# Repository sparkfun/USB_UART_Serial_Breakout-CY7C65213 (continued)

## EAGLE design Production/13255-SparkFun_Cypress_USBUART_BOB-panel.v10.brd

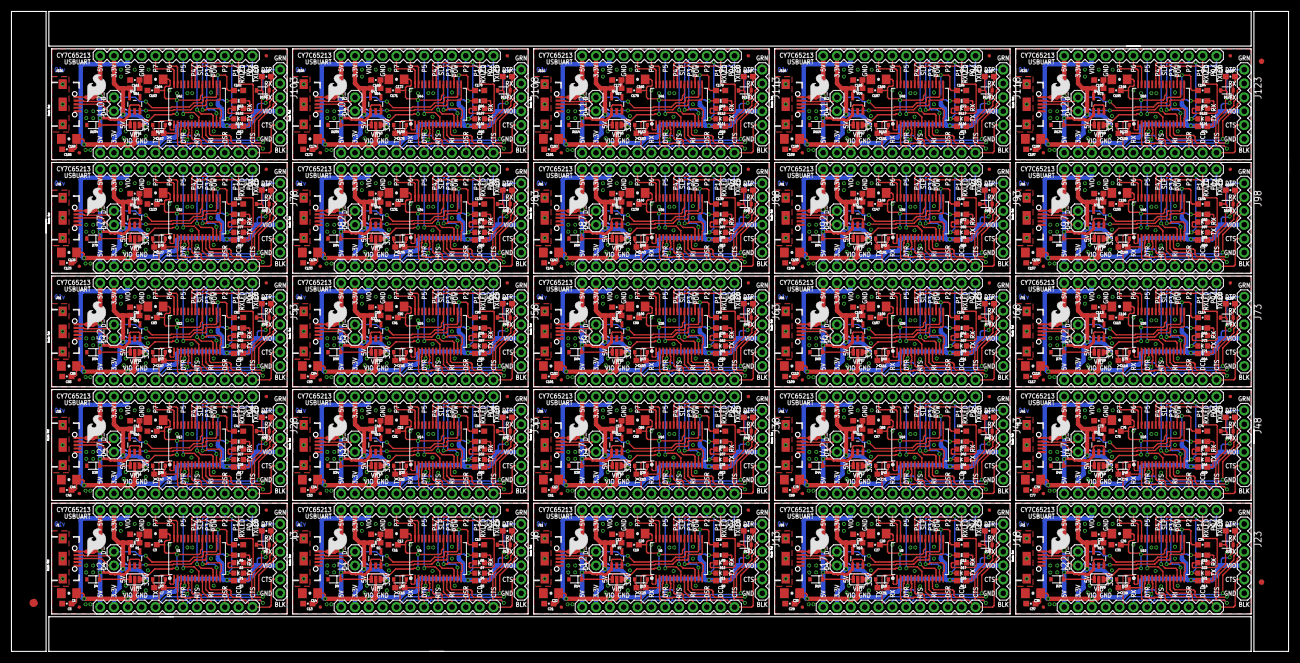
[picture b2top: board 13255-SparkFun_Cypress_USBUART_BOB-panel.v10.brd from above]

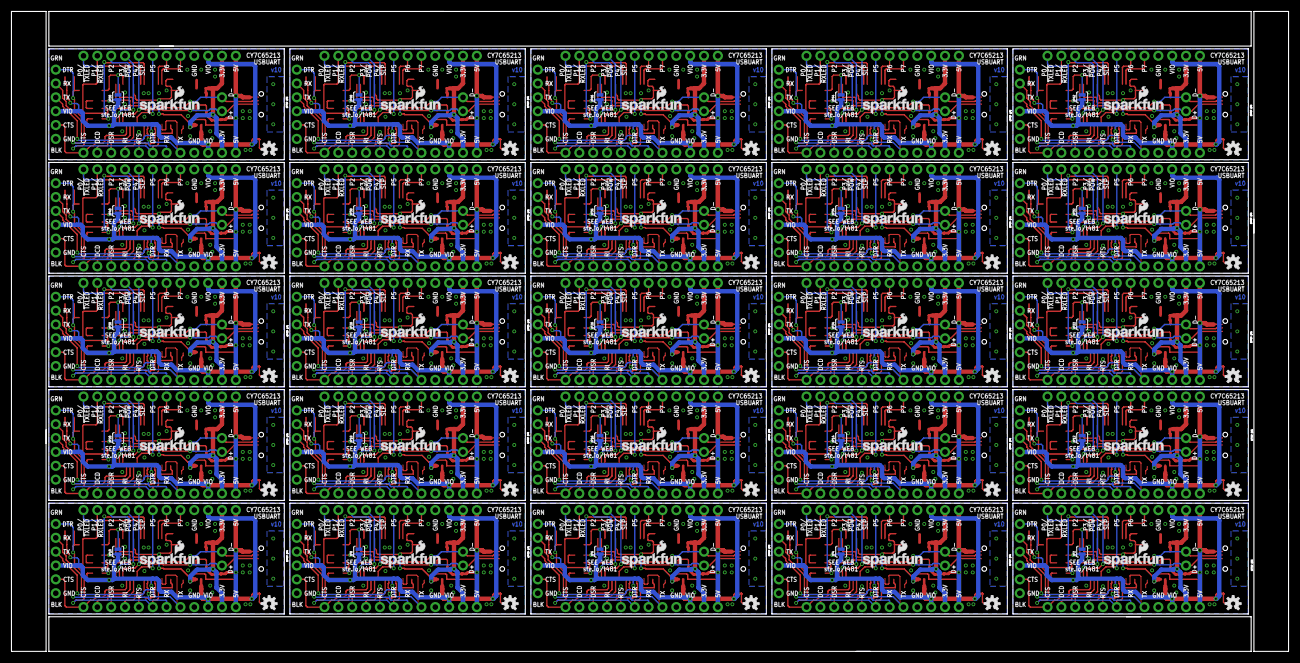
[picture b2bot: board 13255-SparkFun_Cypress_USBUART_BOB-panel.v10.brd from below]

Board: 2 copper layers, 234.2 x 117.3 mm, 753 parts (75 on the bottom side), 675 nets.

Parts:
C1, C9, C17, C25, C33, C41, C49, C57, C65, C73, C81, C89, C97, C105, C113, C121, C129, C137, C145, C153, C161, C169, C177, C185, C193: 2.2uF; 0603-CAP
C2, C10, C18, C26, C34, C42, C50, C58, C66, C74, C82, C90, C98, C106, C114, C122, C130, C138, C146, C154, C162, C170, C178, C186, C194: 1.0uF; 0603-CAP
C3, C5, C11, C13, C19, C21, C27, C29, C35, C37, C43, C45, C51, C53, C59, C61, C67, C69, C75, C77, C83, C85, C91, C93, C99, C101, C107, C109, C115, C117, C123, C125, C131, C133, C139, C141, C147, C149, C155, C157, C163, C165, C171, C173, C179, C181, C187, C189, C195, C197: 0.1uF; 0603-CAP
C4, C6, C12, C14, C20, C22, C28, C30, C36, C38, C44, C46, C52, C54, C60, C62, C68, C70, C76, C78, C84, C86, C92, C94, C100, C102, C108, C110, C116, C118, C124, C126, C132, C134, C140, C142, C148, C150, C156, C158, C164, C166, C172, C174, C180, C182, C188, C190, C196, C198: 4.7uF; 1206-CAP
C7, C8, C15, C16, C23, C24, C31, C32, C39, C40, C47, C48, C55, C56, C63, C64, C71, C72, C79, C80, C87, C88, C95, C96, C103, C104, C111, C112, C119, C120, C127, C128, C135, C136, C143, C144, C151, C152, C159, C160, C167, C168, C175, C176, C183, C184, C191, C192, C199, C200: 10pF; 0603-CAP
D1, D6, D11, D16, D21, D26, D31, D36, D41, D46, D51, D56, D61, D66, D71, D76, D81, D86, D91, D96, D101, D106, D111, D116, D121: RED; LED-0603
D2, D7, D12, D17, D22, D27, D32, D37, D42, D47, D52, D57, D62, D67, D72, D77, D82, D87, D92, D97, D102, D107, D112, D117, D122: GREEN; LED-0603
D3, D5, D8, D10, D13, D15, D18, D20, D23, D25, D28, D30, D33, D35, D38, D40, D43, D45, D48, D50, D53, D55, D58, D60, D63, D65, D68, D70, D73, D75, D78, D80, D83, D85, D88, D90, D93, D95, D98, D100, D103, D105, D108, D110, D113, D115, D118, D120, D123, D125: PMEG4005EJ; SOD-323
D4, D9, D14, D19, D24, D29, D34, D39, D44, D49, D54, D59, D64, D69, D74, D79, D84, D89, D94, D99, D104, D109, D114, D119, D124: 5.6V; SOD-323
E$1: FIDUCIAL-1.5X3
E$7, E$8: FIDUCIAL-1X2
FD1, FD2, FD3, FD4, FD5, FD6, FD7, FD8, FD9, FD10, FD11, FD12, FD13, FD14, FD15, FD16, FD17, FD18, FD19, FD20, FD21, FD22, FD23, FD24, FD25, FD26, FD27, FD28, FD29, FD30, FD31, FD32, FD33, FD34, FD35, FD36, FD37, FD38, FD39, FD40, FD41, FD42, FD43, FD44, FD45, FD46, FD47, FD48, FD49, FD50: FIDUCIALUFIDUCIAL; MICRO-FIDUCIAL
J1, J6, J11, J16, J21, J26, J31, J36, J41, J46, J51, J56, J61, J66, J71, J76, J81, J86, J91, J96, J101, J106, J111, J116, J121: MICROB; USB-B-MICRO-SMD_V03
J2, J7, J12, J17, J22, J27, J32, J37, J42, J47, J52, J57, J62, J67, J72, J77, J82, J87, J92, J97, J102, J107, J112, J117, J122: 1X02
J3, J8, J13, J18, J23, J28, J33, J38, J43, J48, J53, J58, J63, J68, J73, J78, J83, J88, J93, J98, J103, J108, J113, J118, J123: FTDI_BASICPTH; FTDI_BASIC
J4, J5, J9, J10, J14, J15, J19, J20, J24, J25, J29, J30, J34, J35, J39, J40, J44, J45, J49, J50, J54, J55, J59, J60, J64, J65, J69, J70, J74, J75, J79, J80, J84, J85, J89, J90, J94, J95, J99, J100, J104, J105, J109, J110, J114, J115, J119, J120, J124, J125: 1X12
JP1, JP3, JP5, JP7, JP9, JP11, JP13, JP15, JP17, JP19, JP21, JP23, JP25, JP27, JP29, JP31, JP33, JP35, JP37, JP39, JP41, JP43, JP45, JP47, JP49: JUMPER-PAD-3-2OF3_NC_BY_PASTE; PAD-JUMPER-3-2OF3_NC_BY_PASTE_YES_SILK_FULL_BOX
JP2, JP4, JP6, JP8, JP10, JP12, JP14, JP16, JP18, JP20, JP22, JP24, JP26, JP28, JP30, JP32, JP34, JP36, JP38, JP40, JP42, JP44, JP46, JP48, JP50: JUMPER-PAD-2-NOYES_SILK; PAD-JUMPER-2-NO_YES_SILK
LOGO1, LOGO3, LOGO7, LOGO10, LOGO13, LOGO16, LOGO19, LOGO22, LOGO25, LOGO28, LOGO31, LOGO34, LOGO37, LOGO40, LOGO43, LOGO46, LOGO49, LOGO52, LOGO55, LOGO58, LOGO61, LOGO64, LOGO67, LOGO70, LOGO73: SFE_LOGO_NAME_FLAME.1_INCH; SFE_LOGO_NAME_FLAME_.1
LOGO2, LOGO6, LOGO9, LOGO12, LOGO15, LOGO18, LOGO21, LOGO24, LOGO27, LOGO30, LOGO33, LOGO36, LOGO39, LOGO42, LOGO45, LOGO48, LOGO51, LOGO54, LOGO57, LOGO60, LOGO63, LOGO66, LOGO69, LOGO72, LOGO75: OSHW-LOGOS; OSHW-LOGO-S
LOGO4, LOGO5, LOGO8, LOGO11, LOGO14, LOGO17, LOGO20, LOGO23, LOGO26, LOGO29, LOGO32, LOGO35, LOGO38, LOGO41, LOGO44, LOGO47, LOGO50, LOGO53, LOGO56, LOGO59, LOGO62, LOGO65, LOGO68, LOGO71, LOGO74: SFE_LOGO_FLAME.2_INCH; SFE_LOGO_FLAME_.2
R1, R2, R7, R10, R13, R16, R19, R22, R25, R28, R31, R34, R37, R40, R43, R46, R49, R52, R55, R58, R61, R64, R67, R70, R73: 0.27; 0603-RES
R3, R4, R5, R6, R8, R9, R11, R12, R14, R15, R17, R18, R20, R21, R23, R24, R26, R27, R29, R30, R32, R33, R35, R36, R38, R39, R41, R42, R44, R45, R47, R48, R50, R51, R53, R54, R56, R57, R59, R60, R62, R63, R65, R66, R68, R69, R71, R72, R74, R75: 1K; 0603-RES
U1, U4, U6, U8, U10, U12, U14, U16, U18, U20, U22, U24, U26, U28, U30, U32, U34, U36, U38, U40, U42, U44, U46, U48, U50: CY7C65213; SSOP28DB
U2, U3, U5, U7, U9, U11, U13, U15, U17, U19, U21, U23, U25, U27, U29, U31, U33, U35, U37, U39, U41, U43, U45, U47, U49: 3.3V; SOT23-5

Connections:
3.3V: J4.11, J5.11, JP1.1, R1.2, U2.5
3.3V1: J9.11, J10.11, JP3.1, R2.2, U3.5
3.3V2: J14.11, J15.11, JP5.1, R7.2, U5.5
3.3V3: J19.11, J20.11, JP7.1, R10.2, U7.5
3.3V4: J24.11, J25.11, JP9.1, R13.2, U9.5
3.3V5: J29.11, J30.11, JP11.1, R16.2, U11.5
3.3V6: J34.11, J35.11, JP13.1, R19.2, U13.5
3.3V7: J39.11, J40.11, JP15.1, R22.2, U15.5
3.3V8: J44.11, J45.11, JP17.1, R25.2, U17.5
3.3V9: J49.11, J50.11, JP19.1, R28.2, U19.5
3.3V10: J54.11, J55.11, JP21.1, R31.2, U21.5
3.3V11: J59.11, J60.11, JP23.1, R34.2, U23.5
3.3V12: J64.11, J65.11, JP25.1, R37.2, U25.5
3.3V13: J69.11, J70.11, JP27.1, R40.2, U27.5
3.3V14: J74.11, J75.11, JP29.1, R43.2, U29.5
3.3V15: J79.11, J80.11, JP31.1, R46.2, U31.5
3.3V16: J84.11, J85.11, JP33.1, R49.2, U33.5
3.3V17: J89.11, J90.11, JP35.1, R52.2, U35.5
3.3V18: J94.11, J95.11, JP37.1, R55.2, U37.5
3.3V19: J99.11, J100.11, JP39.1, R58.2, U39.5
3.3V20: J104.11, J105.11, JP41.1, R61.2, U41.5
3.3V21: J109.11, J110.11, JP43.1, R64.2, U43.5
3.3V22: J114.11, J115.11, JP45.1, R67.2, U45.5
3.3V23: J119.11, J120.11, JP47.1, R70.2, U47.5
3.3V24: J124.11, J125.11, JP49.1, R73.2, U49.5
5V: C3.1, C4.1, D4.C, J1.VBUS1, J4.12, J5.12, JP1.3, U1.20, U2.1, U2.3
5V1: C11.1, C12.1, D9.C, J6.VBUS1, J9.12, J10.12, JP3.3, U3.1, U3.3, U4.20
5V2: C19.1, C20.1, D14.C, J11.VBUS1, J14.12, J15.12, JP5.3, U5.1, U5.3, U6.20
5V3: C27.1, C28.1, D19.C, J16.VBUS1, J19.12, J20.12, JP7.3, U7.1, U7.3, U8.20
5V4: C35.1, C36.1, D24.C, J21.VBUS1, J24.12, J25.12, JP9.3, U9.1, U9.3, U10.20
5V5: C43.1, C44.1, D29.C, J26.VBUS1, J29.12, J30.12, JP11.3, U11.1, U11.3, U12.20
5V6: C51.1, C52.1, D34.C, J31.VBUS1, J34.12, J35.12, JP13.3, U13.1, U13.3, U14.20
5V7: C59.1, C60.1, D39.C, J36.VBUS1, J39.12, J40.12, JP15.3, U15.1, U15.3, U16.20
5V8: C67.1, C68.1, D44.C, J41.VBUS1, J44.12, J45.12, JP17.3, U17.1, U17.3, U18.20
5V9: C75.1, C76.1, D49.C, J46.VBUS1, J49.12, J50.12, JP19.3, U19.1, U19.3, U20.20
5V10: C83.1, C84.1, D54.C, J51.VBUS1, J54.12, J55.12, JP21.3, U21.1, U21.3, U22.20
5V11: C91.1, C92.1, D59.C, J56.VBUS1, J59.12, J60.12, JP23.3, U23.1, U23.3, U24.20
5V12: C99.1, C100.1, D64.C, J61.VBUS1, J64.12, J65.12, JP25.3, U25.1, U25.3, U26.20
5V13: C107.1, C108.1, D69.C, J66.VBUS1, J69.12, J70.12, JP27.3, U27.1, U27.3, U28.20
5V14: C115.1, C116.1, D74.C, J71.VBUS1, J74.12, J75.12, JP29.3, U29.1, U29.3, U30.20
5V15: C123.1, C124.1, D79.C, J76.VBUS1, J79.12, J80.12, JP31.3, U31.1, U31.3, U32.20
5V16: C131.1, C132.1, D84.C, J81.VBUS1, J84.12, J85.12, JP33.3, U33.1, U33.3, U34.20
5V17: C139.1, C140.1, D89.C, J86.VBUS1, J89.12, J90.12, JP35.3, U35.1, U35.3, U36.20
5V18: C147.1, C148.1, D94.C, J91.VBUS1, J94.12, J95.12, JP37.3, U37.1, U37.3, U38.20
5V19: C155.1, C156.1, D99.C, J96.VBUS1, J99.12, J100.12, JP39.3, U39.1, U39.3, U40.20
5V20: C163.1, C164.1, D104.C, J101.VBUS1, J104.12, J105.12, JP41.3, U41.1, U41.3, U42.20
5V21: C171.1, C172.1, D109.C, J106.VBUS1, J109.12, J110.12, JP43.3, U43.1, U43.3, U44.20
5V22: C179.1, C180.1, D114.C, J111.VBUS1, J114.12, J115.12, JP45.3, U45.1, U45.3, U46.20
5V23: C187.1, C188.1, D119.C, J116.VBUS1, J119.12, J120.12, JP47.3, U47.1, U47.3, U48.20
5V24: C195.1, C196.1, D124.C, J121.VBUS1, J124.12, J125.12, JP49.3, U49.1, U49.3, U50.20
CTS: J3.CTS, J4.1, U1.11
CTS1: J8.CTS, J9.1, U4.11
CTS2: J13.CTS, J14.1, U6.11
CTS3: J18.CTS, J19.1, U8.11
CTS4: J23.CTS, J24.1, U10.11
CTS5: J28.CTS, J29.1, U12.11
CTS6: J33.CTS, J34.1, U14.11
CTS7: J38.CTS, J39.1, U16.11
CTS8: J43.CTS, J44.1, U18.11
CTS9: J48.CTS, J49.1, U20.11
CTS10: J53.CTS, J54.1, U22.11
CTS11: J58.CTS, J59.1, U24.11
CTS12: J63.CTS, J64.1, U26.11
CTS13: J68.CTS, J69.1, U28.11
CTS14: J73.CTS, J74.1, U30.11
CTS15: J78.CTS, J79.1, U32.11
CTS16: J83.CTS, J84.1, U34.11
CTS17: J88.CTS, J89.1, U36.11
CTS18: J93.CTS, J94.1, U38.11
CTS19: J98.CTS, J99.1, U40.11
CTS20: J103.CTS, J104.1, U42.11
CTS21: J108.CTS, J109.1, U44.11
CTS22: J113.CTS, J114.1, U46.11
CTS23: J118.CTS, J119.1, U48.11
CTS24: J123.CTS, J124.1, U50.11
D+: J1.D+1, J2.1, U1.15
D+1: J6.D+1, J7.1, U4.15
D+2: J11.D+1, J12.1, U6.15
D+3: J16.D+1, J17.1, U8.15
D+4: J21.D+1, J22.1, U10.15
D+5: J26.D+1, J27.1, U12.15
D+6: J31.D+1, J32.1, U14.15
D+7: J36.D+1, J37.1, U16.15
D+8: J41.D+1, J42.1, U18.15
D+9: J46.D+1, J47.1, U20.15
D+10: J51.D+1, J52.1, U22.15
D+11: J56.D+1, J57.1, U24.15
D+12: J61.D+1, J62.1, U26.15
D+13: J66.D+1, J67.1, U28.15
D+14: J71.D+1, J72.1, U30.15
D+15: J76.D+1, J77.1, U32.15
D+16: J81.D+1, J82.1, U34.15
D+17: J86.D+1, J87.1, U36.15
D+18: J91.D+1, J92.1, U38.15
D+19: J96.D+1, J97.1, U40.15
D+20: J101.D+1, J102.1, U42.15
D+21: J106.D+1, J107.1, U44.15
D+22: J111.D+1, J112.1, U46.15
D+23: J116.D+1, J117.1, U48.15
D+24: J121.D+1, J122.1, U50.15
D-: J1.D-1, J2.2, U1.16
D-1: J6.D-1, J7.2, U4.16
D-2: J11.D-1, J12.2, U6.16
D-3: J16.D-1, J17.2, U8.16
D-4: J21.D-1, J22.2, U10.16
D-5: J26.D-1, J27.2, U12.16
D-6: J31.D-1, J32.2, U14.16
D-7: J36.D-1, J37.2, U16.16
D-8: J41.D-1, J42.2, U18.16
D-9: J46.D-1, J47.2, U20.16
D-10: J51.D-1, J52.2, U22.16
D-11: J56.D-1, J57.2, U24.16
D-12: J61.D-1, J62.2, U26.16
D-13: J66.D-1, J67.2, U28.16
D-14: J71.D-1, J72.2, U30.16
D-15: J76.D-1, J77.2, U32.16
D-16: J81.D-1, J82.2, U34.16
D-17: J86.D-1, J87.2, U36.16
D-18: J91.D-1, J92.2, U38.16
D-19: J96.D-1, J97.2, U40.16
D-20: J101.D-1, J102.2, U42.16
D-21: J106.D-1, J107.2, U44.16
D-22: J111.D-1, J112.2, U46.16
D-23: J116.D-1, J117.2, U48.16
D-24: J121.D-1, J122.2, U50.16
DCD: J4.2, U1.10
DCD1: J9.2, U4.10
DCD2: J14.2, U6.10
DCD3: J19.2, U8.10
DCD4: J24.2, U10.10
DCD5: J29.2, U12.10
DCD6: J34.2, U14.10
DCD7: J39.2, U16.10
DCD8: J44.2, U18.10
DCD9: J49.2, U20.10
DCD10: J54.2, U22.10
DCD11: J59.2, U24.10
DCD12: J64.2, U26.10
DCD13: J69.2, U28.10
DCD14: J74.2, U30.10
DCD15: J79.2, U32.10
DCD16: J84.2, U34.10
DCD17: J89.2, U36.10
DCD18: J94.2, U38.10
DCD19: J99.2, U40.10
DCD20: J104.2, U42.10
DCD21: J109.2, U44.10
DCD22: J114.2, U46.10
DCD23: J119.2, U48.10
DCD24: J124.2, U50.10
DSR: J4.3, U1.9
DSR1: J9.3, U4.9
DSR2: J14.3, U6.9
DSR3: J19.3, U8.9
DSR4: J24.3, U10.9
DSR5: J29.3, U12.9
DSR6: J34.3, U14.9
DSR7: J39.3, U16.9
DSR8: J44.3, U18.9
DSR9: J49.3, U20.9
DSR10: J54.3, U22.9
DSR11: J59.3, U24.9
DSR12: J64.3, U26.9
DSR13: J69.3, U28.9
DSR14: J74.3, U30.9
DSR15: J79.3, U32.9
DSR16: J84.3, U34.9
DSR17: J89.3, U36.9
DSR18: J94.3, U38.9
DSR19: J99.3, U40.9
DSR20: J104.3, U42.9
DSR21: J109.3, U44.9
DSR22: J114.3, U46.9
DSR23: J119.3, U48.9
DSR24: J124.3, U50.9
DTR: C7.1, C8.1, D3.C, D5.A, J3.DTR, J4.6, U1.2
DTR1: C15.1, C16.1, D8.C, D10.A, J8.DTR, J9.6, U4.2
DTR2: C23.1, C24.1, D13.C, D15.A, J13.DTR, J14.6, U6.2
DTR3: C31.1, C32.1, D18.C, D20.A, J18.DTR, J19.6, U8.2
DTR4: C39.1, C40.1, D23.C, D25.A, J23.DTR, J24.6, U10.2
DTR5: C47.1, C48.1, D28.C, D30.A, J28.DTR, J29.6, U12.2
DTR6: C55.1, C56.1, D33.C, D35.A, J33.DTR, J34.6, U14.2
DTR7: C63.1, C64.1, D38.C, D40.A, J38.DTR, J39.6, U16.2
DTR8: C71.1, C72.1, D43.C, D45.A, J43.DTR, J44.6, U18.2
DTR9: C79.1, C80.1, D48.C, D50.A, J48.DTR, J49.6, U20.2
DTR10: C87.1, C88.1, D53.C, D55.A, J53.DTR, J54.6, U22.2
DTR11: C95.1, C96.1, D58.C, D60.A, J58.DTR, J59.6, U24.2
DTR12: C103.1, C104.1, D63.C, D65.A, J63.DTR, J64.6, U26.2
DTR13: C111.1, C112.1, D68.C, D70.A, J68.DTR, J69.6, U28.2
DTR14: C119.1, C120.1, D73.C, D75.A, J73.DTR, J74.6, U30.2
DTR15: C127.1, C128.1, D78.C, D80.A, J78.DTR, J79.6, U32.2
DTR16: C135.1, C136.1, D83.C, D85.A, J83.DTR, J84.6, U34.2
DTR17: C143.1, C144.1, D88.C, D90.A, J88.DTR, J89.6, U36.2
DTR18: C151.1, C152.1, D93.C, D95.A, J93.DTR, J94.6, U38.2
DTR19: C159.1, C160.1, D98.C, D100.A, J98.DTR, J99.6, U40.2
DTR20: C167.1, C168.1, D103.C, D105.A, J103.DTR, J104.6, U42.2
DTR21: C175.1, C176.1, D108.C, D110.A, J108.DTR, J109.6, U44.2
DTR22: C183.1, C184.1, D113.C, D115.A, J113.DTR, J114.6, U46.2
DTR23: C191.1, C192.1, D118.C, D120.A, J118.DTR, J119.6, U48.2
DTR24: C199.1, C200.1, D123.C, D125.A, J123.DTR, J124.6, U50.2
GND: C1.2, C2.2, C3.2, C4.2, C5.2, C6.2, C7.2, D3.A, D4.A, J1.GND1, J3.GND, J4.9, J5.9, U1.7, U1.18, U1.21, U2.2
GND1: C9.2, C10.2, C11.2, C12.2, C13.2, C14.2, C15.2, D8.A, D9.A, J6.GND1, J8.GND, J9.9, J10.9, U3.2, U4.7, U4.18, U4.21
GND2: C17.2, C18.2, C19.2, C20.2, C21.2, C22.2, C23.2, D13.A, D14.A, J11.GND1, J13.GND, J14.9, J15.9, U5.2, U6.7, U6.18, U6.21
GND3: C25.2, C26.2, C27.2, C28.2, C29.2, C30.2, C31.2, D18.A, D19.A, J16.GND1, J18.GND, J19.9, J20.9, U7.2, U8.7, U8.18, U8.21
GND4: C33.2, C34.2, C35.2, C36.2, C37.2, C38.2, C39.2, D23.A, D24.A, J21.GND1, J23.GND, J24.9, J25.9, U9.2, U10.7, U10.18, U10.21
GND5: C41.2, C42.2, C43.2, C44.2, C45.2, C46.2, C47.2, D28.A, D29.A, J26.GND1, J28.GND, J29.9, J30.9, U11.2, U12.7, U12.18, U12.21
GND6: C49.2, C50.2, C51.2, C52.2, C53.2, C54.2, C55.2, D33.A, D34.A, J31.GND1, J33.GND, J34.9, J35.9, U13.2, U14.7, U14.18, U14.21
GND7: C57.2, C58.2, C59.2, C60.2, C61.2, C62.2, C63.2, D38.A, D39.A, J36.GND1, J38.GND, J39.9, J40.9, U15.2, U16.7, U16.18, U16.21
GND8: C65.2, C66.2, C67.2, C68.2, C69.2, C70.2, C71.2, D43.A, D44.A, J41.GND1, J43.GND, J44.9, J45.9, U17.2, U18.7, U18.18, U18.21
GND9: C73.2, C74.2, C75.2, C76.2, C77.2, C78.2, C79.2, D48.A, D49.A, J46.GND1, J48.GND, J49.9, J50.9, U19.2, U20.7, U20.18, U20.21
GND10: C81.2, C82.2, C83.2, C84.2, C85.2, C86.2, C87.2, D53.A, D54.A, J51.GND1, J53.GND, J54.9, J55.9, U21.2, U22.7, U22.18, U22.21
GND11: C89.2, C90.2, C91.2, C92.2, C93.2, C94.2, C95.2, D58.A, D59.A, J56.GND1, J58.GND, J59.9, J60.9, U23.2, U24.7, U24.18, U24.21
GND12: C97.2, C98.2, C99.2, C100.2, C101.2, C102.2, C103.2, D63.A, D64.A, J61.GND1, J63.GND, J64.9, J65.9, U25.2, U26.7, U26.18, U26.21
GND13: C105.2, C106.2, C107.2, C108.2, C109.2, C110.2, C111.2, D68.A, D69.A, J66.GND1, J68.GND, J69.9, J70.9, U27.2, U28.7, U28.18, U28.21
GND14: C113.2, C114.2, C115.2, C116.2, C117.2, C118.2, C119.2, D73.A, D74.A, J71.GND1, J73.GND, J74.9, J75.9, U29.2, U30.7, U30.18, U30.21
GND15: C121.2, C122.2, C123.2, C124.2, C125.2, C126.2, C127.2, D78.A, D79.A, J76.GND1, J78.GND, J79.9, J80.9, U31.2, U32.7, U32.18, U32.21
GND16: C129.2, C130.2, C131.2, C132.2, C133.2, C134.2, C135.2, D83.A, D84.A, J81.GND1, J83.GND, J84.9, J85.9, U33.2, U34.7, U34.18, U34.21
GND17: C137.2, C138.2, C139.2, C140.2, C141.2, C142.2, C143.2, D88.A, D89.A, J86.GND1, J88.GND, J89.9, J90.9, U35.2, U36.7, U36.18, U36.21
GND18: C145.2, C146.2, C147.2, C148.2, C149.2, C150.2, C151.2, D93.A, D94.A, J91.GND1, J93.GND, J94.9, J95.9, U37.2, U38.7, U38.18, U38.21
GND19: C153.2, C154.2, C155.2, C156.2, C157.2, C158.2, C159.2, D98.A, D99.A, J96.GND1, J98.GND, J99.9, J100.9, U39.2, U40.7, U40.18, U40.21
GND20: C161.2, C162.2, C163.2, C164.2, C165.2, C166.2, C167.2, D103.A, D104.A, J101.GND1, J103.GND, J104.9, J105.9, U41.2, U42.7, U42.18, U42.21
GND21: C169.2, C170.2, C171.2, C172.2, C173.2, C174.2, C175.2, D108.A, D109.A, J106.GND1, J108.GND, J109.9, J110.9, U43.2, U44.7, U44.18, U44.21
GND22: C177.2, C178.2, C179.2, C180.2, C181.2, C182.2, C183.2, D113.A, D114.A, J111.GND1, J113.GND, J114.9, J115.9, U45.2, U46.7, U46.18, U46.21
GND23: C185.2, C186.2, C187.2, C188.2, C189.2, C190.2, C191.2, D118.A, D119.A, J116.GND1, J118.GND, J119.9, J120.9, U47.2, U48.7, U48.18, U48.21
GND24: C193.2, C194.2, C195.2, C196.2, C197.2, C198.2, C199.2, D123.A, D124.A, J121.GND1, J123.GND, J124.9, J125.9, U49.2, U50.7, U50.18, U50.21
GPIO0: D1.C, J5.1, U1.23
GPIO1: D2.C, J5.2, U1.22
GPIO2: J5.3, U1.13
GPIO3: J5.4, U1.14
GPIO4: J5.5, U1.12
GPIO5: J5.6, U1.8
GPIO6: J5.7, U1.27
GPIO7: J5.8, U1.28
GPIO8: J10.7, U4.27
GPIO9: J10.8, U4.28
GPIO10: D6.C, J10.1, U4.23
GPIO11: D7.C, J10.2, U4.22
GPIO12: J10.4, U4.14
GPIO13: J10.3, U4.13
GPIO14: J10.5, U4.12
GPIO15: J10.6, U4.8
GPIO16: J15.7, U6.27
GPIO17: J15.8, U6.28
GPIO18: D11.C, J15.1, U6.23
GPIO19: D12.C, J15.2, U6.22
GPIO20: J15.4, U6.14
GPIO21: J15.3, U6.13
GPIO22: J15.5, U6.12
GPIO23: J15.6, U6.8
GPIO24: J20.7, U8.27
GPIO25: J20.8, U8.28
GPIO26: D16.C, J20.1, U8.23
GPIO27: D17.C, J20.2, U8.22
GPIO28: J20.4, U8.14
GPIO29: J20.3, U8.13
GPIO30: J20.5, U8.12
GPIO31: J20.6, U8.8
GPIO32: J25.7, U10.27
GPIO33: J25.8, U10.28
GPIO34: D21.C, J25.1, U10.23
GPIO35: D22.C, J25.2, U10.22
GPIO36: J25.4, U10.14
GPIO37: J25.3, U10.13
GPIO38: J25.5, U10.12
GPIO39: J25.6, U10.8
GPIO40: J30.7, U12.27
GPIO41: J30.8, U12.28
GPIO42: D26.C, J30.1, U12.23
GPIO43: D27.C, J30.2, U12.22
GPIO44: J30.4, U12.14
GPIO45: J30.3, U12.13
GPIO46: J30.5, U12.12
GPIO47: J30.6, U12.8
GPIO48: J35.7, U14.27
GPIO49: J35.8, U14.28
GPIO50: D31.C, J35.1, U14.23
GPIO51: D32.C, J35.2, U14.22
GPIO52: J35.4, U14.14
GPIO53: J35.3, U14.13
GPIO54: J35.5, U14.12
GPIO55: J35.6, U14.8
GPIO56: J40.7, U16.27
GPIO57: J40.8, U16.28
GPIO58: D36.C, J40.1, U16.23
GPIO59: D37.C, J40.2, U16.22
GPIO60: J40.4, U16.14
GPIO61: J40.3, U16.13
GPIO62: J40.5, U16.12
GPIO63: J40.6, U16.8
GPIO64: J45.7, U18.27
GPIO65: J45.8, U18.28
GPIO66: D41.C, J45.1, U18.23
GPIO67: D42.C, J45.2, U18.22
GPIO68: J45.4, U18.14
GPIO69: J45.3, U18.13
GPIO70: J45.5, U18.12
GPIO71: J45.6, U18.8
GPIO72: J50.7, U20.27
GPIO73: J50.8, U20.28
GPIO74: D46.C, J50.1, U20.23
GPIO75: D47.C, J50.2, U20.22
GPIO76: J50.4, U20.14
GPIO77: J50.3, U20.13
GPIO78: J50.5, U20.12
GPIO79: J50.6, U20.8
GPIO80: J55.7, U22.27
GPIO81: J55.8, U22.28
GPIO82: D51.C, J55.1, U22.23
GPIO83: D52.C, J55.2, U22.22
GPIO84: J55.4, U22.14
GPIO85: J55.3, U22.13
GPIO86: J55.5, U22.12
GPIO87: J55.6, U22.8
GPIO88: J60.7, U24.27
GPIO89: J60.8, U24.28
GPIO90: D56.C, J60.1, U24.23
GPIO91: D57.C, J60.2, U24.22
GPIO92: J60.4, U24.14
GPIO93: J60.3, U24.13
GPIO94: J60.5, U24.12
GPIO95: J60.6, U24.8
GPIO96: J65.7, U26.27
GPIO97: J65.8, U26.28
GPIO98: D61.C, J65.1, U26.23
GPIO99: D62.C, J65.2, U26.22
GPIO100: J65.4, U26.14
GPIO101: J65.3, U26.13
GPIO102: J65.5, U26.12
GPIO103: J65.6, U26.8
GPIO104: J70.7, U28.27
GPIO105: J70.8, U28.28
GPIO106: D66.C, J70.1, U28.23
GPIO107: D67.C, J70.2, U28.22
GPIO108: J70.4, U28.14
GPIO109: J70.3, U28.13
GPIO110: J70.5, U28.12
GPIO111: J70.6, U28.8
GPIO112: J75.7, U30.27
GPIO113: J75.8, U30.28
GPIO114: D71.C, J75.1, U30.23
GPIO115: D72.C, J75.2, U30.22
GPIO116: J75.4, U30.14
GPIO117: J75.3, U30.13
GPIO118: J75.5, U30.12
GPIO119: J75.6, U30.8
GPIO120: J80.7, U32.27
GPIO121: J80.8, U32.28
GPIO122: D76.C, J80.1, U32.23
GPIO123: D77.C, J80.2, U32.22
GPIO124: J80.4, U32.14
GPIO125: J80.3, U32.13
GPIO126: J80.5, U32.12
GPIO127: J80.6, U32.8
GPIO128: J85.7, U34.27
GPIO129: J85.8, U34.28
GPIO130: D81.C, J85.1, U34.23
GPIO131: D82.C, J85.2, U34.22
GPIO132: J85.4, U34.14
GPIO133: J85.3, U34.13
GPIO134: J85.5, U34.12
GPIO135: J85.6, U34.8
GPIO136: J90.7, U36.27
GPIO137: J90.8, U36.28
GPIO138: D86.C, J90.1, U36.23
GPIO139: D87.C, J90.2, U36.22
GPIO140: J90.4, U36.14
GPIO141: J90.3, U36.13
GPIO142: J90.5, U36.12
GPIO143: J90.6, U36.8
GPIO144: J95.7, U38.27
GPIO145: J95.8, U38.28
GPIO146: D91.C, J95.1, U38.23
GPIO147: D92.C, J95.2, U38.22
GPIO148: J95.4, U38.14
GPIO149: J95.3, U38.13
GPIO150: J95.5, U38.12
GPIO151: J95.6, U38.8
GPIO152: J100.7, U40.27
GPIO153: J100.8, U40.28
GPIO154: D96.C, J100.1, U40.23
GPIO155: D97.C, J100.2, U40.22
GPIO156: J100.4, U40.14
GPIO157: J100.3, U40.13
GPIO158: J100.5, U40.12
GPIO159: J100.6, U40.8
GPIO160: J105.7, U42.27
GPIO161: J105.8, U42.28
GPIO162: D101.C, J105.1, U42.23
GPIO163: D102.C, J105.2, U42.22
GPIO164: J105.4, U42.14
GPIO165: J105.3, U42.13
GPIO166: J105.5, U42.12
GPIO167: J105.6, U42.8
GPIO168: J110.7, U44.27
GPIO169: J110.8, U44.28
GPIO170: D106.C, J110.1, U44.23
GPIO171: D107.C, J110.2, U44.22
GPIO172: J110.4, U44.14
GPIO173: J110.3, U44.13
GPIO174: J110.5, U44.12
GPIO175: J110.6, U44.8
GPIO176: J115.7, U46.27
GPIO177: J115.8, U46.28
GPIO178: D111.C, J115.1, U46.23
GPIO179: D112.C, J115.2, U46.22
GPIO180: J115.4, U46.14
GPIO181: J115.3, U46.13
GPIO182: J115.5, U46.12
GPIO183: J115.6, U46.8
GPIO184: J120.7, U48.27
GPIO185: J120.8, U48.28
GPIO186: D116.C, J120.1, U48.23
GPIO187: D117.C, J120.2, U48.22
GPIO188: J120.4, U48.14
GPIO189: J120.3, U48.13
GPIO190: J120.5, U48.12
GPIO191: J120.6, U48.8
GPIO192: J125.7, U50.27
GPIO193: J125.8, U50.28
GPIO194: D121.C, J125.1, U50.23
GPIO195: D122.C, J125.2, U50.22
GPIO196: J125.4, U50.14
GPIO197: J125.3, U50.13
GPIO198: J125.5, U50.12
GPIO199: J125.6, U50.8
unnamed: C1.1, R1.1
unnamed: D2.A, R4.1
unnamed: D1.A, R3.1
unnamed: C9.1, R2.1
unnamed: D7.A, R6.1
unnamed: D6.A, R5.1
unnamed: C17.1, R7.1
unnamed: D12.A, R9.1
unnamed: D11.A, R8.1
unnamed: C25.1, R10.1
unnamed: D17.A, R12.1
unnamed: D16.A, R11.1
unnamed: C33.1, R13.1
unnamed: D22.A, R15.1
unnamed: D21.A, R14.1
unnamed: C41.1, R16.1
unnamed: D27.A, R18.1
unnamed: D26.A, R17.1
unnamed: C49.1, R19.1
unnamed: D32.A, R21.1
unnamed: D31.A, R20.1
unnamed: C57.1, R22.1
unnamed: D37.A, R24.1
unnamed: D36.A, R23.1
unnamed: C65.1, R25.1
unnamed: D42.A, R27.1
unnamed: D41.A, R26.1
unnamed: C73.1, R28.1
unnamed: D47.A, R30.1
unnamed: D46.A, R29.1
unnamed: C81.1, R31.1
unnamed: D52.A, R33.1
unnamed: D51.A, R32.1
unnamed: C89.1, R34.1
unnamed: D57.A, R36.1
unnamed: D56.A, R35.1
unnamed: C97.1, R37.1
unnamed: D62.A, R39.1
unnamed: D61.A, R38.1
unnamed: C105.1, R40.1
unnamed: D67.A, R42.1
unnamed: D66.A, R41.1
unnamed: C113.1, R43.1
unnamed: D72.A, R45.1
unnamed: D71.A, R44.1
unnamed: C121.1, R46.1
unnamed: D77.A, R48.1
unnamed: D76.A, R47.1
unnamed: C129.1, R49.1
unnamed: D82.A, R51.1
unnamed: D81.A, R50.1
unnamed: C137.1, R52.1
unnamed: D87.A, R54.1
unnamed: D86.A, R53.1
unnamed: C145.1, R55.1
unnamed: D92.A, R57.1
unnamed: D91.A, R56.1
unnamed: C153.1, R58.1
unnamed: D97.A, R60.1
unnamed: D96.A, R59.1
unnamed: C161.1, R61.1
unnamed: D102.A, R63.1
unnamed: D101.A, R62.1
unnamed: C169.1, R64.1
unnamed: D107.A, R66.1
unnamed: D106.A, R65.1
unnamed: C177.1, R67.1
unnamed: D112.A, R69.1
unnamed: D111.A, R68.1
unnamed: C185.1, R70.1
unnamed: D117.A, R72.1
unnamed: D116.A, R71.1
unnamed: C193.1, R73.1
unnamed: D122.A, R75.1
unnamed: D121.A, R74.1
RI: J4.4, U1.6
RI1: J9.4, U4.6
RI2: J14.4, U6.6
RI3: J19.4, U8.6
RI4: J24.4, U10.6
RI5: J29.4, U12.6
RI6: J34.4, U14.6
RI7: J39.4, U16.6
RI8: J44.4, U18.6
RI9: J49.4, U20.6
RI10: J54.4, U22.6
RI11: J59.4, U24.6
RI12: J64.4, U26.6
RI13: J69.4, U28.6
RI14: J74.4, U30.6
RI15: J79.4, U32.6
RI16: J84.4, U34.6
RI17: J89.4, U36.6
RI18: J94.4, U38.6
RI19: J99.4, U40.6
RI20: J104.4, U42.6
RI21: J109.4, U44.6
RI22: J114.4, U46.6
RI23: J119.4, U48.6
RI24: J124.4, U50.6
RTS: J4.5, U1.3
RTS1: J9.5, U4.3
RTS2: J14.5, U6.3
RTS3: J19.5, U8.3
RTS4: J24.5, U10.3
RTS5: J29.5, U12.3
RTS6: J34.5, U14.3
RTS7: J39.5, U16.3
RTS8: J44.5, U18.3
RTS9: J49.5, U20.3
RTS10: J54.5, U22.3
RTS11: J59.5, U24.3
RTS12: J64.5, U26.3
RTS13: J69.5, U28.3
RTS14: J74.5, U30.3
RTS15: J79.5, U32.3
RTS16: J84.5, U34.3
RTS17: J89.5, U36.3
RTS18: J94.5, U38.3
RTS19: J99.5, U40.3
RTS20: J104.5, U42.3
RTS21: J109.5, U44.3
RTS22: J114.5, U46.3
RTS23: J119.5, U48.3
RTS24: J124.5, U50.3
RXD: J3.RXI, J4.7, U1.5
RXD1: J8.RXI, J9.7, U4.5
RXD2: J13.RXI, J14.7, U6.5
RXD3: J18.RXI, J19.7, U8.5
RXD4: J23.RXI, J24.7, U10.5
RXD5: J28.RXI, J29.7, U12.5
RXD6: J33.RXI, J34.7, U14.5
RXD7: J38.RXI, J39.7, U16.5
RXD8: J43.RXI, J44.7, U18.5
RXD9: J48.RXI, J49.7, U20.5
RXD10: J53.RXI, J54.7, U22.5
RXD11: J58.RXI, J59.7, U24.5
RXD12: J63.RXI, J64.7, U26.5
RXD13: J68.RXI, J69.7, U28.5
RXD14: J73.RXI, J74.7, U30.5
RXD15: J78.RXI, J79.7, U32.5
RXD16: J83.RXI, J84.7, U34.5
RXD17: J88.RXI, J89.7, U36.5
RXD18: J93.RXI, J94.7, U38.5
RXD19: J98.RXI, J99.7, U40.5
RXD20: J103.RXI, J104.7, U42.5
RXD21: J108.RXI, J109.7, U44.5
RXD22: J113.RXI, J114.7, U46.5
RXD23: J118.RXI, J119.7, U48.5
RXD24: J123.RXI, J124.7, U50.5
SHIELD_POUR: J1.SHIELD1, J1.SHIELD2, J1.SHIELD3
SHIELD_POUR1: J6.SHIELD1, J6.SHIELD2, J6.SHIELD3
SHIELD_POUR2: J11.SHIELD1, J11.SHIELD2, J11.SHIELD3
SHIELD_POUR3: J16.SHIELD1, J16.SHIELD2, J16.SHIELD3
SHIELD_POUR4: J21.SHIELD1, J21.SHIELD2, J21.SHIELD3
SHIELD_POUR5: J26.SHIELD1, J26.SHIELD2, J26.SHIELD3
SHIELD_POUR6: J31.SHIELD1, J31.SHIELD2, J31.SHIELD3
SHIELD_POUR7: J36.SHIELD1, J36.SHIELD2, J36.SHIELD3
SHIELD_POUR8: J41.SHIELD1, J41.SHIELD2, J41.SHIELD3
SHIELD_POUR9: J46.SHIELD1, J46.SHIELD2, J46.SHIELD3
SHIELD_POUR10: J51.SHIELD1, J51.SHIELD2, J51.SHIELD3
SHIELD_POUR11: J56.SHIELD1, J56.SHIELD2, J56.SHIELD3
SHIELD_POUR12: J61.SHIELD1, J61.SHIELD2, J61.SHIELD3
SHIELD_POUR13: J66.SHIELD1, J66.SHIELD2, J66.SHIELD3
SHIELD_POUR14: J71.SHIELD1, J71.SHIELD2, J71.SHIELD3
SHIELD_POUR15: J76.SHIELD1, J76.SHIELD2, J76.SHIELD3
SHIELD_POUR16: J81.SHIELD1, J81.SHIELD2, J81.SHIELD3
SHIELD_POUR17: J86.SHIELD1, J86.SHIELD2, J86.SHIELD3
SHIELD_POUR18: J91.SHIELD1, J91.SHIELD2, J91.SHIELD3
SHIELD_POUR19: J96.SHIELD1, J96.SHIELD2, J96.SHIELD3
SHIELD_POUR20: J101.SHIELD1, J101.SHIELD2, J101.SHIELD3
SHIELD_POUR21: J106.SHIELD1, J106.SHIELD2, J106.SHIELD3
SHIELD_POUR22: J111.SHIELD1, J111.SHIELD2, J111.SHIELD3
SHIELD_POUR23: J116.SHIELD1, J116.SHIELD2, J116.SHIELD3
SHIELD_POUR24: J121.SHIELD1, J121.SHIELD2, J121.SHIELD3
TXD: J3.TXO, J4.8, U1.1
TXD1: J8.TXO, J9.8, U4.1
TXD2: J13.TXO, J14.8, U6.1
TXD3: J18.TXO, J19.8, U8.1
TXD4: J23.TXO, J24.8, U10.1
TXD5: J28.TXO, J29.8, U12.1
TXD6: J33.TXO, J34.8, U14.1
TXD7: J38.TXO, J39.8, U16.1
TXD8: J43.TXO, J44.8, U18.1
TXD9: J48.TXO, J49.8, U20.1
TXD10: J53.TXO, J54.8, U22.1
TXD11: J58.TXO, J59.8, U24.1
TXD12: J63.TXO, J64.8, U26.1
TXD13: J68.TXO, J69.8, U28.1
TXD14: J73.TXO, J74.8, U30.1
TXD15: J78.TXO, J79.8, U32.1
TXD16: J83.TXO, J84.8, U34.1
TXD17: J88.TXO, J89.8, U36.1
TXD18: J93.TXO, J94.8, U38.1
TXD19: J98.TXO, J99.8, U40.1
TXD20: J103.TXO, J104.8, U42.1
TXD21: J108.TXO, J109.8, U44.1
TXD22: J113.TXO, J114.8, U46.1
TXD23: J118.TXO, J119.8, U48.1
TXD24: J123.TXO, J124.8, U50.1
VCCIO: C5.1, C6.1, C8.2, D5.C, J3.VCC, J4.10, J5.10, JP1.2, JP2.1, R3.2, R4.2, U1.4
VCCIO1: C13.1, C14.1, C16.2, D10.C, J8.VCC, J9.10, J10.10, JP3.2, JP4.1, R5.2, R6.2, U4.4
VCCIO2: C21.1, C22.1, C24.2, D15.C, J13.VCC, J14.10, J15.10, JP5.2, JP6.1, R8.2, R9.2, U6.4
VCCIO3: C29.1, C30.1, C32.2, D20.C, J18.VCC, J19.10, J20.10, JP7.2, JP8.1, R11.2, R12.2, U8.4
VCCIO4: C37.1, C38.1, C40.2, D25.C, J23.VCC, J24.10, J25.10, JP9.2, JP10.1, R14.2, R15.2, U10.4
VCCIO5: C45.1, C46.1, C48.2, D30.C, J28.VCC, J29.10, J30.10, JP11.2, JP12.1, R17.2, R18.2, U12.4
VCCIO6: C53.1, C54.1, C56.2, D35.C, J33.VCC, J34.10, J35.10, JP13.2, JP14.1, R20.2, R21.2, U14.4
VCCIO7: C61.1, C62.1, C64.2, D40.C, J38.VCC, J39.10, J40.10, JP15.2, JP16.1, R23.2, R24.2, U16.4
VCCIO8: C69.1, C70.1, C72.2, D45.C, J43.VCC, J44.10, J45.10, JP17.2, JP18.1, R26.2, R27.2, U18.4
VCCIO9: C77.1, C78.1, C80.2, D50.C, J48.VCC, J49.10, J50.10, JP19.2, JP20.1, R29.2, R30.2, U20.4
VCCIO10: C85.1, C86.1, C88.2, D55.C, J53.VCC, J54.10, J55.10, JP21.2, JP22.1, R32.2, R33.2, U22.4
VCCIO11: C93.1, C94.1, C96.2, D60.C, J58.VCC, J59.10, J60.10, JP23.2, JP24.1, R35.2, R36.2, U24.4
VCCIO12: C101.1, C102.1, C104.2, D65.C, J63.VCC, J64.10, J65.10, JP25.2, JP26.1, R38.2, R39.2, U26.4
VCCIO13: C109.1, C110.1, C112.2, D70.C, J68.VCC, J69.10, J70.10, JP27.2, JP28.1, R41.2, R42.2, U28.4
VCCIO14: C117.1, C118.1, C120.2, D75.C, J73.VCC, J74.10, J75.10, JP29.2, JP30.1, R44.2, R45.2, U30.4
VCCIO15: C125.1, C126.1, C128.2, D80.C, J78.VCC, J79.10, J80.10, JP31.2, JP32.1, R47.2, R48.2, U32.4
VCCIO16: C133.1, C134.1, C136.2, D85.C, J83.VCC, J84.10, J85.10, JP33.2, JP34.1, R50.2, R51.2, U34.4
VCCIO17: C141.1, C142.1, C144.2, D90.C, J88.VCC, J89.10, J90.10, JP35.2, JP36.1, R53.2, R54.2, U36.4
VCCIO18: C149.1, C150.1, C152.2, D95.C, J93.VCC, J94.10, J95.10, JP37.2, JP38.1, R56.2, R57.2, U38.4
VCCIO19: C157.1, C158.1, C160.2, D100.C, J98.VCC, J99.10, J100.10, JP39.2, JP40.1, R59.2, R60.2, U40.4
VCCIO20: C165.1, C166.1, C168.2, D105.C, J103.VCC, J104.10, J105.10, JP41.2, JP42.1, R62.2, R63.2, U42.4
VCCIO21: C173.1, C174.1, C176.2, D110.C, J108.VCC, J109.10, J110.10, JP43.2, JP44.1, R65.2, R66.2, U44.4
VCCIO22: C181.1, C182.1, C184.2, D115.C, J113.VCC, J114.10, J115.10, JP45.2, JP46.1, R68.2, R69.2, U46.4
VCCIO23: C189.1, C190.1, C192.2, D120.C, J118.VCC, J119.10, J120.10, JP47.2, JP48.1, R71.2, R72.2, U48.4
VCCIO24: C197.1, C198.1, C200.2, D125.C, J123.VCC, J124.10, J125.10, JP49.2, JP50.1, R74.2, R75.2, U50.4
VDD: C2.1, JP2.2, U1.17
VDD1: C10.1, JP4.2, U4.17
VDD2: C18.1, JP6.2, U6.17
VDD3: C26.1, JP8.2, U8.17
VDD4: C34.1, JP10.2, U10.17
VDD5: C42.1, JP12.2, U12.17
VDD6: C50.1, JP14.2, U14.17
VDD7: C58.1, JP16.2, U16.17
VDD8: C66.1, JP18.2, U18.17
VDD9: C74.1, JP20.2, U20.17
VDD10: C82.1, JP22.2, U22.17
VDD11: C90.1, JP24.2, U24.17
VDD12: C98.1, JP26.2, U26.17
VDD13: C106.1, JP28.2, U28.17
VDD14: C114.1, JP30.2, U30.17
VDD15: C122.1, JP32.2, U32.17
VDD16: C130.1, JP34.2, U34.17
VDD17: C138.1, JP36.2, U36.17
VDD18: C146.1, JP38.2, U38.17
VDD19: C154.1, JP40.2, U40.17
VDD20: C162.1, JP42.2, U42.17
VDD21: C170.1, JP44.2, U44.17
VDD22: C178.1, JP46.2, U46.17
VDD23: C186.1, JP48.2, U48.17
VDD24: C194.1, JP50.2, U50.17

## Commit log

2016-02-15 Add gitignore
2016-02-15 Ready for QC review
2016-02-15 Fixed another insufficiently bent trace
2016-03-29 Rotate a couple of parts, add 10k resistor, v02
2016-06-28 Changes from review incorporated
2016-08-02 Changed version number for reds
2016-08-18 Revert to v02.
    Revert "Changed version number for reds"
    This reverts commit 640f5162c93cb70f6f1d384f505e534c75df1209.
2016-08-18 Revert to v02
2016-08-19 Feedback from group review, add clamping diodes
2016-08-19 Remove 15-ohm resistor in power line
2016-08-22 Changes from group review
2016-09-09 Update to v10, ready for reds
2016-11-07 panel
2017-02-02 updating readme
